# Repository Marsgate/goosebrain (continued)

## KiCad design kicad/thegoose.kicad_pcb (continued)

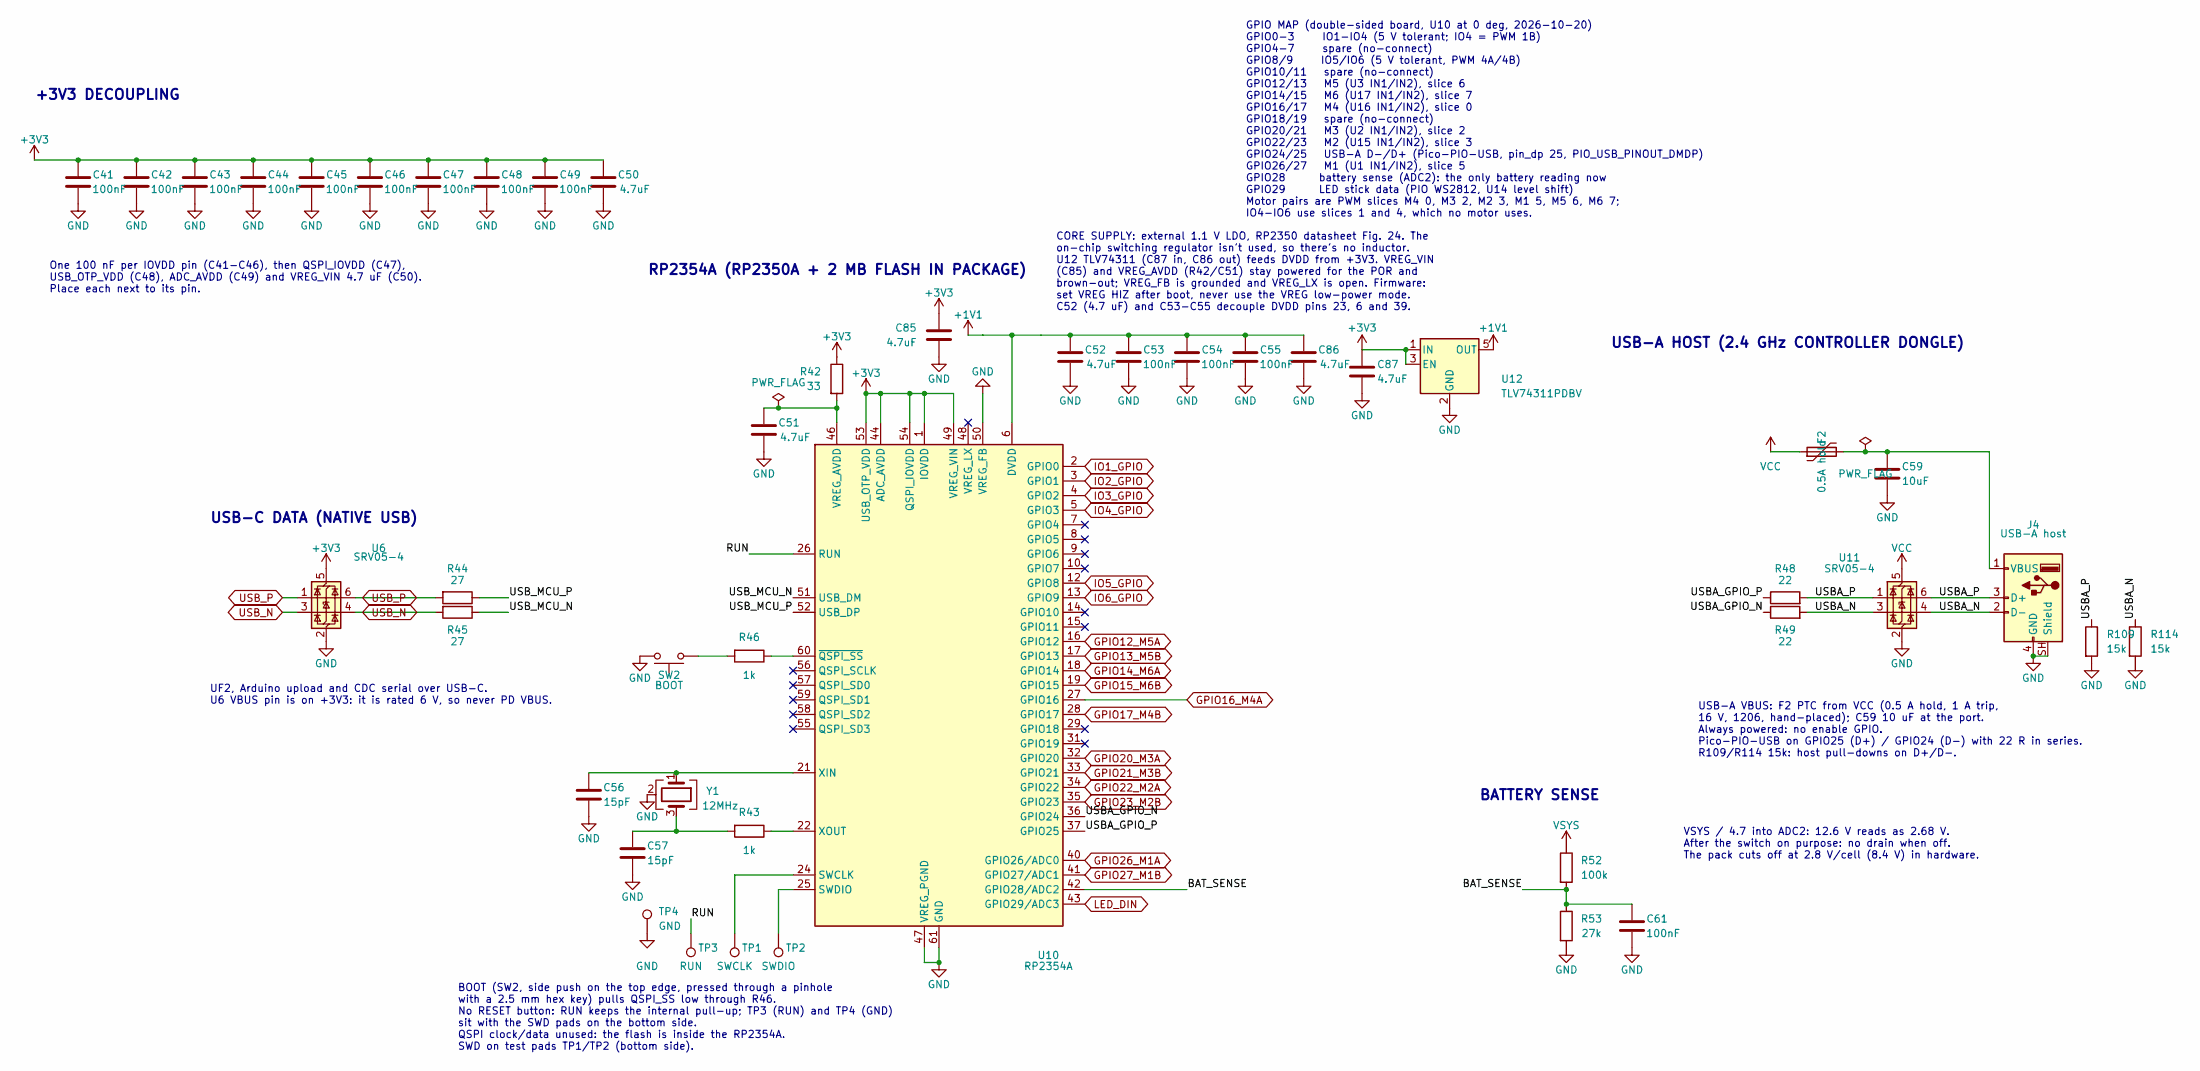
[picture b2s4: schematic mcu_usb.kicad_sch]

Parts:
C41, C42, C43, C44, C45, C46, C47, C48, C49, C53, C54, C55, C61: 100nF; C_0402_1005Metric; MPN CL05B104KO5NNNC; LCSC Part # C1525
C50, C51, C52, C85, C86, C87: 4.7uF; C_0402_1005Metric; MPN CL05A475MP5NRNC; LCSC Part # C23733
C56, C57: 15pF; C_0402_1005Metric; MPN 0402CG150J500NT; LCSC Part # C1548
C59: 10uF; C_0805_2012Metric; MPN CL21A106KAYNNNE; LCSC Part # C15850
F2: 0.5A hold; Fuse_1206_3216Metric; MPN JK-nSMD050-16; LCSC Part # C2680506
J4: USB-A host; USB_A_ShouHan_AF90_WJDG; MPN AF 90 WJDG; LCSC Part # C456018
R42: 33; R_0402_1005Metric; MPN 0402WGF330JTCE; LCSC Part # C25105
R43, R46: 1k; R_0402_1005Metric; MPN 0402WGF1001TCE; LCSC Part # C11702
R44, R45: 27; R_0603_1608Metric; MPN 0603WAF270JT5E; LCSC Part # C25190
R48, R49: 22; R_0402_1005Metric; MPN 0402WGF220JTCE; LCSC Part # C25092
R52: 100k; R_0402_1005Metric; MPN 0402WGF1003TCE; LCSC Part # C25741
R53: 27k; R_0402_1005Metric; MPN 0402WGF2702TCE; LCSC Part # C25771
R109, R114: 15k; R_0402_1005Metric; MPN 0402WGF1502TCE; LCSC Part # C25756
SW2: BOOT; SW_Push_1P1T-MP_NO_Horizontal_Alps_SKRTLAE010_JLC; MPN SKRTLAE010; LCSC Part # C110293
TP1: SWCLK; TestPoint_Pad_D1.0mm
TP2: SWDIO; TestPoint_Pad_D1.0mm
TP3: RUN; TestPoint_Pad_D1.0mm
TP4: GND; TestPoint_Pad_D1.0mm
U6, U11: SRV05-4; SOT-23-6; MPN SRV05-4; LCSC Part # C7420376
U10: RP2354A; QFN-60-1EP_7x7mm_P0.4mm_EP3.4x3.4mm; MPN RP2354A; LCSC Part # C41378174
U12: TLV74311PDBV; SOT-23-5; MPN TLV74311PDBVR; LCSC Part # C485147
Y1: 12MHz; Crystal_SMD_3225-4Pin_3.2x2.5mm; MPN ABM8-272-T3; LCSC Part # C20625731

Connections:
+1V1: C52.1, C53.1, C54.1, C55.1, C86.1, U10.6 (DVDD), U10.23 (DVDD), U10.39 (DVDD), U12.5 (OUT)
+3V3: C41.1, C42.1, C43.1, C44.1, C45.1, C46.1, C47.1, C48.1, C49.1, C50.1, C85.1, C87.1, R42.1, U6.5 (VP), U10.1 (IOVDD), U10.11 (IOVDD), U10.20 (IOVDD), U10.30 (IOVDD), U10.38 (IOVDD), U10.44 (ADC_AVDD), U10.45 (IOVDD), U10.49 (VREG_VIN), U10.53 (USB_OTP_VDD), U10.54 (QSPI_IOVDD), U12.1 (IN), U12.3 (EN); also elsewhere on the board
/MCU & USB/BAT_SENSE: C61.1, R52.2, R53.1, U10.42 (GPIO28/ADC2)
/MCU & USB/RUN: TP3.1 (1_1), U10.26 (RUN)
/MCU & USB/USBA_GPIO_N: R49.1, U10.36 (GPIO24)
/MCU & USB/USBA_GPIO_P: R48.1, U10.37 (GPIO25)
/MCU & USB/USBA_N: J4.2 (D-), R49.2, R114.1, U11.3 (IO2), U11.4 (IO3)
/MCU & USB/USBA_P: J4.3 (D+), R48.2, R109.1, U11.1 (IO1), U11.6 (IO4)
/MCU & USB/USB_MCU_N: R45.1, U10.51 (USB_DM)
/MCU & USB/USB_MCU_P: R44.1, U10.52 (USB_DP)
GND: C41.2, C42.2, C43.2, C44.2, C45.2, C46.2, C47.2, C48.2, C49.2, C50.2, C51.2, C52.2, C53.2, C54.2, C55.2, C56.2, C57.2, C59.2, C61.2, C85.2, C86.2, C87.2, J4.4 (GND), J4.SH (Shield), R53.2, R109.2, R114.2, SW2.2, TP4.1 (1_1), U6.2 (VN), U10.47 (VREG_PGND), U10.50 (VREG_FB), U10.61 (GND), U11.2 (VN), U12.2 (GND), Y1.2 (G), Y1.4 (G); also elsewhere on the board
GPIO12_M5A: U10.16 (GPIO12); also elsewhere on the board
GPIO13_M5B: U10.17 (GPIO13); also elsewhere on the board
GPIO14_M6A: U10.18 (GPIO14); also elsewhere on the board
GPIO15_M6B: U10.19 (GPIO15); also elsewhere on the board
GPIO16_M4A: U10.27 (GPIO16); also elsewhere on the board
GPIO17_M4B: U10.28 (GPIO17); also elsewhere on the board
GPIO20_M3A: U10.32 (GPIO20); also elsewhere on the board
GPIO21_M3B: U10.33 (GPIO21); also elsewhere on the board
GPIO22_M2A: U10.34 (GPIO22); also elsewhere on the board
GPIO23_M2B: U10.35 (GPIO23); also elsewhere on the board
GPIO26_M1A: U10.40 (GPIO26/ADC0); also elsewhere on the board
GPIO27_M1B: U10.41 (GPIO27/ADC1); also elsewhere on the board
IO1_GPIO: U10.2 (GPIO0); also elsewhere on the board
IO2_GPIO: U10.3 (GPIO1); also elsewhere on the board
IO3_GPIO: U10.4 (GPIO2); also elsewhere on the board
IO4_GPIO: U10.5 (GPIO3); also elsewhere on the board
IO5_GPIO: U10.12 (GPIO8); also elsewhere on the board
IO6_GPIO: U10.13 (GPIO9); also elsewhere on the board
LED_DIN: U10.43 (GPIO29/ADC3); also elsewhere on the board
unnamed: C57.1, R43.2, Y1.3
unnamed: C59.1, F2.2, J4.1 (VBUS)
unnamed: R46.2, SW2.1
unnamed: TP1.1 (1_1), U10.24 (SWCLK)
unnamed: TP2.1 (1_1), U10.25 (SWDIO)
unnamed: C51.1, R42.2, U10.46 (VREG_AVDD)
unnamed: C56.1, U10.21 (XIN), Y1.1
unnamed: R43.1, U10.22 (XOUT)
unnamed: R46.1, U10.60 (~QSPI_SS)
USB_N: R45.2, U6.3 (IO2), U6.4 (IO3); also elsewhere on the board
USB_P: R44.2, U6.1 (IO1), U6.6 (IO4); also elsewhere on the board
VCC: F2.1, U11.5 (VP); also elsewhere on the board
VSYS: R52.1; also elsewhere on the board

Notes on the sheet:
RP2354A (RP2350A + 2 MB FLASH IN PACKAGE)
UF2, Arduino upload and CDC serial over USB-C. U6 VBUS pin is on +3V3: it is rated 6 V, so never PD VBUS.
+3V3 DECOUPLING
CORE SUPPLY: external 1.1 V LDO, RP2350 datasheet Fig. 24. The on-chip switching regulator isn't used, so there's no inductor. U12 TLV74311 (C87 in, C86 out) feeds DVDD from +3V3. VREG_VIN (C85) and VREG_AVDD (R42/C51) stay powered for the POR and brown-out; VREG_FB is grounded and VREG_LX is open.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
BATTERY SENSE
VSYS / 4.7 into ADC2: 12.6 V reads as 2.68 V. After the switch on purpose: no drain when off. The pack cuts off at 2.8 V/cell (8.4 V) in hardware.
USB-C DATA (NATIVE USB)
One 100 nF per IOVDD pin (C41-C46), then QSPI_IOVDD (C47), USB_OTP_VDD (C48), ADC_AVDD (C49) and VREG_VIN 4.7 uF (C50). Place each next to its pin.
USB-A VBUS: F2 PTC from VCC (0.5 A hold, 1 A trip, 16 V, 1206, hand-placed); C59 10 uF at the port. Always powered: no enable GPIO. Pico-PIO-USB on GPIO25 (D+) / GPIO24 (D-) with 22 R in series. R109/R114 15k: host pull-downs on D+/D-.
USB-A HOST (2.4 GHz CONTROLLER DONGLE)
BOOT (SW2, side push on the top edge, pressed through a pinhole with a 2.5 mm hex key) pulls QSPI_SS low through R46. No RESET button: RUN keeps the internal pull-up; TP3 (RUN) and TP4 (GND) sit with the SWD pads on the bottom side. QSPI clock/data unused: the flash is inside the RP2354A. SWD on te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
GPIO MAP (double-sided board, U10 at 0 deg, 2026-10-20) GPIO0-3 IO1-IO4 (5 V tolerant; IO4 = PWM 1B) GPIO4-7 spare (no-connect) GPIO8/9 IO5/IO6 (5 V tolerant, PWM 4A/4B) GPIO10/11 spare (no-connect) GPIO12/13 M5 (U3 IN1/IN2), slice 6 GPIO14/15 M6 (U17 IN1/IN2), slice 7 GPIO16/17 M4 (U16 IN1/IN2), s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

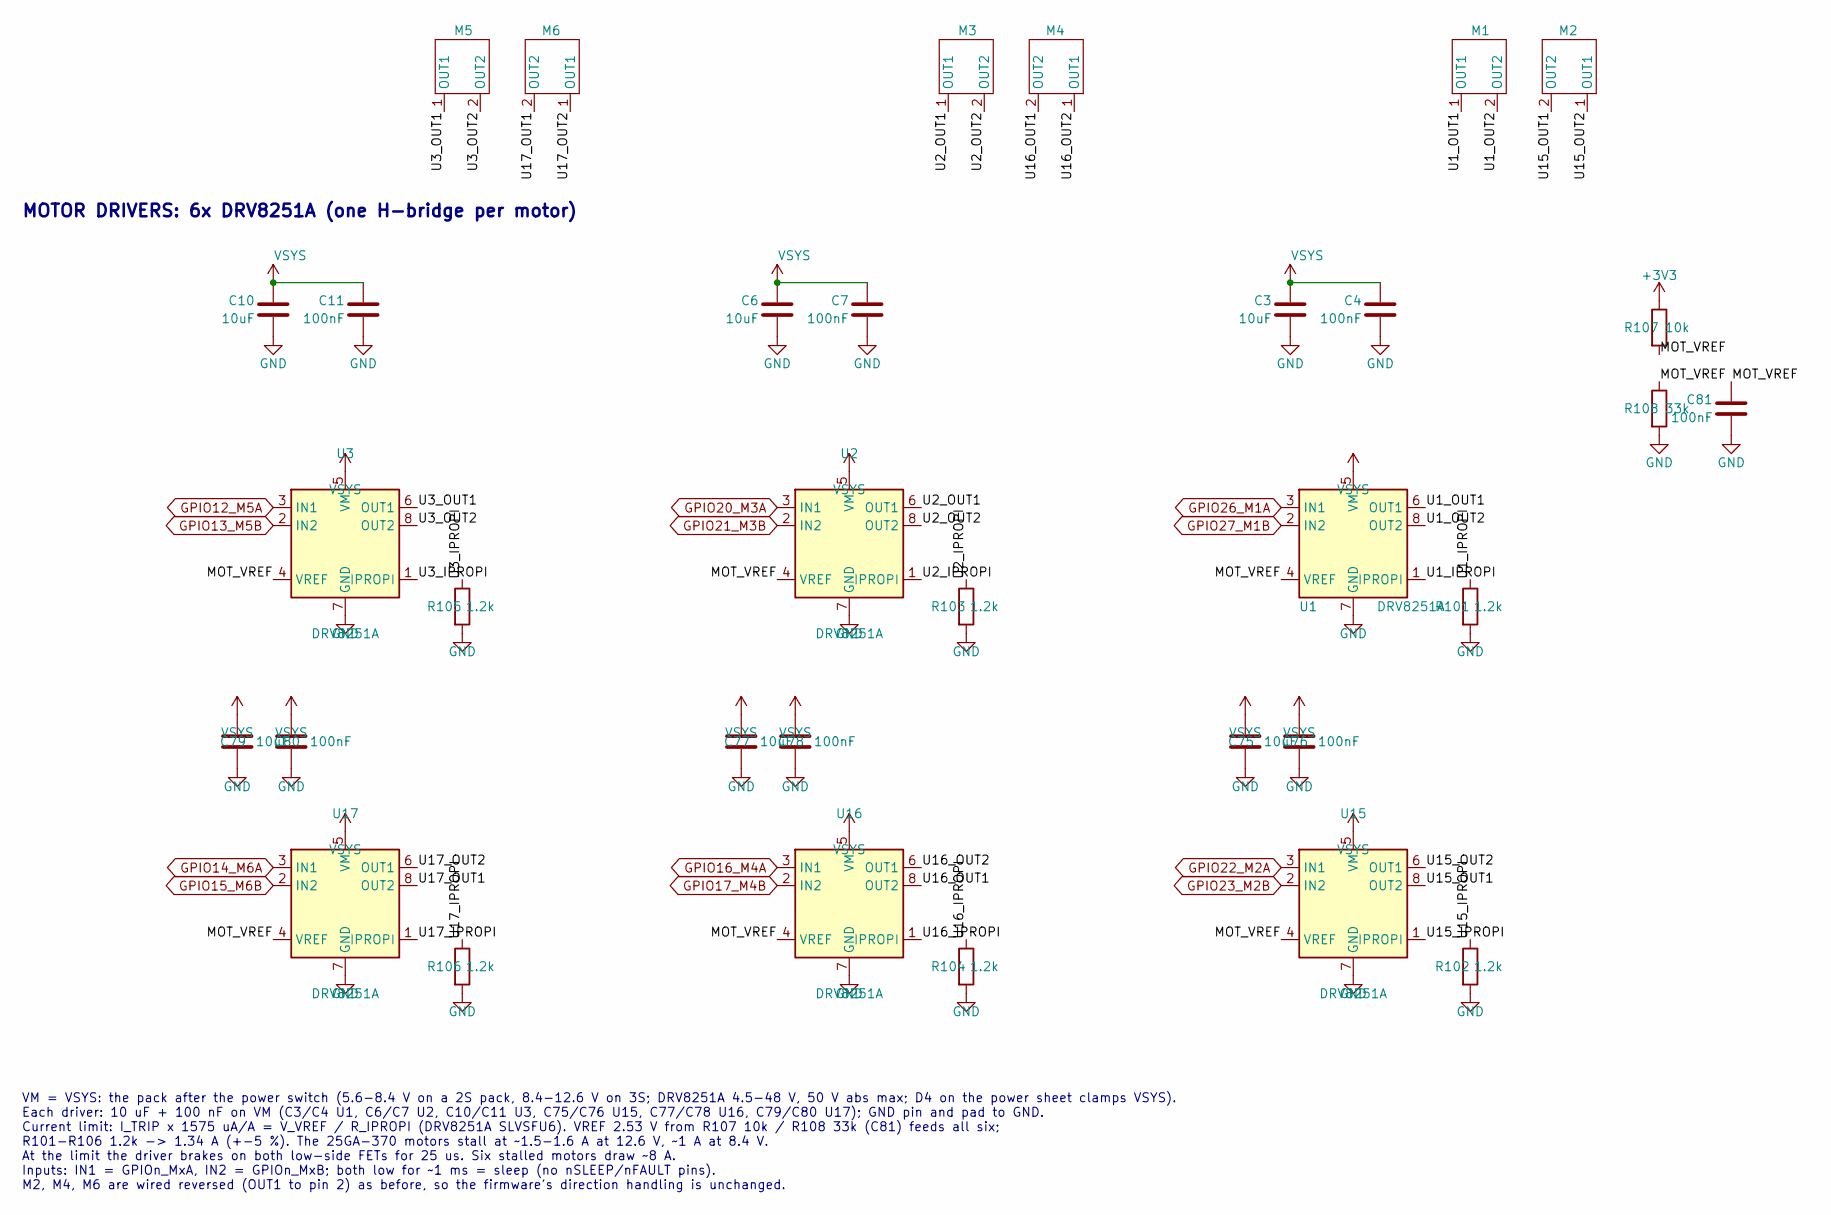
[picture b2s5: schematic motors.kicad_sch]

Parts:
C3, C6, C10, C75, C77, C79: 10uF; C_0805_2012Metric; MPN CL21A106KAYNNNE; LCSC Part # C15850
C4, C7, C11, C76, C78, C80: 100nF; C_0805_2012Metric; MPN CC0805KRX7R9BB104; LCSC Part # C49678
C81: 100nF; C_0402_1005Metric; MPN CL05B104KO5NNNC; LCSC Part # C1525
M1, M2, M3, M4, M5, M6: JST_PH_S2B-PH-K_1x02_P2.00mm_Horizontal; MPN S2B-PH-K-S(LF)(SN); LCSC Part # C173752
R101, R102, R103, R104, R105, R106: 1.2k; R_0402_1005Metric; MPN 0402WGF1201TCE; LCSC Part # C25862
R107: 10k; R_0402_1005Metric; MPN 0402WGF1002TCE; LCSC Part # C25744
R108: 33k; R_0402_1005Metric; MPN 0402WGF3302TCE; LCSC Part # C25779
U1, U2, U3, U15, U16, U17: DRV8251A; Texas_HTSOP-8-1EP_3.9x4.9mm_P1.27mm_EP2.95x4.9mm_Mask2.4x3.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; MPN DRV8251ADDAR; LCSC Part # C5218844

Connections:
+3V3: R107.1; also elsewhere on the board
/Motor drivers/MOT_VREF: C81.1, R107.2, R108.1, U1.4 (VREF), U2.4 (VREF), U3.4 (VREF), U15.4 (VREF), U16.4 (VREF), U17.4 (VREF)
/Motor drivers/U1_IPROPI: R101.1, U1.1 (IPROPI)
/Motor drivers/U1_OUT1: M1.1 (OUT1), U1.6 (OUT1)
/Motor drivers/U1_OUT2: M1.2 (OUT2), U1.8 (OUT2)
/Motor drivers/U2_IPROPI: R103.1, U2.1 (IPROPI)
/Motor drivers/U2_OUT1: M3.1 (OUT1), U2.6 (OUT1)
/Motor drivers/U2_OUT2: M3.2 (OUT2), U2.8 (OUT2)
/Motor drivers/U3_IPROPI: R105.1, U3.1 (IPROPI)
/Motor drivers/U3_OUT1: M5.1 (OUT1), U3.6 (OUT1)
/Motor drivers/U3_OUT2: M5.2 (OUT2), U3.8 (OUT2)
/Motor drivers/U15_IPROPI: R102.1, U15.1 (IPROPI)
/Motor drivers/U15_OUT1: M2.2 (OUT2), U15.8 (OUT2)
/Motor drivers/U15_OUT2: M2.1 (OUT1), U15.6 (OUT1)
/Motor drivers/U16_IPROPI: R104.1, U16.1 (IPROPI)
/Motor drivers/U16_OUT1: M4.2 (OUT2), U16.8 (OUT2)
/Motor drivers/U16_OUT2: M4.1 (OUT1), U16.6 (OUT1)
/Motor drivers/U17_IPROPI: R106.1, U17.1 (IPROPI)
/Motor drivers/U17_OUT1: M6.2 (OUT2), U17.8 (OUT2)
/Motor drivers/U17_OUT2: M6.1 (OUT1), U17.6 (OUT1)
GND: C3.1, C4.2, C6.1, C7.2, C10.1, C11.2, C75.2, C76.2, C77.2, C78.2, C79.2, C80.2, C81.2, R101.2, R102.2, R103.2, R104.2, R105.2, R106.2, R108.2, U1.7 (GND), U1.9 (GND), U2.7 (GND), U2.9 (GND), U3.7 (GND), U3.9 (GND), U15.7 (GND), U15.9 (GND), U16.7 (GND), U16.9 (GND), U17.7 (GND), U17.9 (GND); also elsewhere on the board
GPIO12_M5A: U3.3 (IN1); also elsewhere on the board
GPIO13_M5B: U3.2 (IN2); also elsewhere on the board
GPIO14_M6A: U17.3 (IN1); also elsewhere on the board
GPIO15_M6B: U17.2 (IN2); also elsewhere on the board
GPIO16_M4A: U16.3 (IN1); also elsewhere on the board
GPIO17_M4B: U16.2 (IN2); also elsewhere on the board
GPIO20_M3A: U2.3 (IN1); also elsewhere on the board
GPIO21_M3B: U2.2 (IN2); also elsewhere on the board
GPIO22_M2A: U15.3 (IN1); also elsewhere on the board
GPIO23_M2B: U15.2 (IN2); also elsewhere on the board
GPIO26_M1A: U1.3 (IN1); also elsewhere on the board
GPIO27_M1B: U1.2 (IN2); also elsewhere on the board
VSYS: C3.2, C4.1, C6.2, C7.1, C10.2, C11.1, C75.1, C76.1, C77.1, C78.1, C79.1, C80.1, U1.5 (VM), U2.5 (VM), U3.5 (VM), U15.5 (VM), U16.5 (VM), U17.5 (VM); also elsewhere on the board

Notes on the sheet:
MOTOR DRIVERS: 6x DRV8251A (one H-bridge per motor)
VM = VSYS: the pack after the power switch (5.6-8.4 V on a 2S pack, 8.4-12.6 V on 3S; DRV8251A 4.5-48 V, 50 V abs max; D4 on the power sheet clamps VSYS). Each driver: 10 uF + 100 nF on VM (C3/C4 U1, C6/C7 U2, C10/C11 U3, C75/C76 U15, C77/C78 U16, C79/C80 U17); GND pin and pad to GND. Current limit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

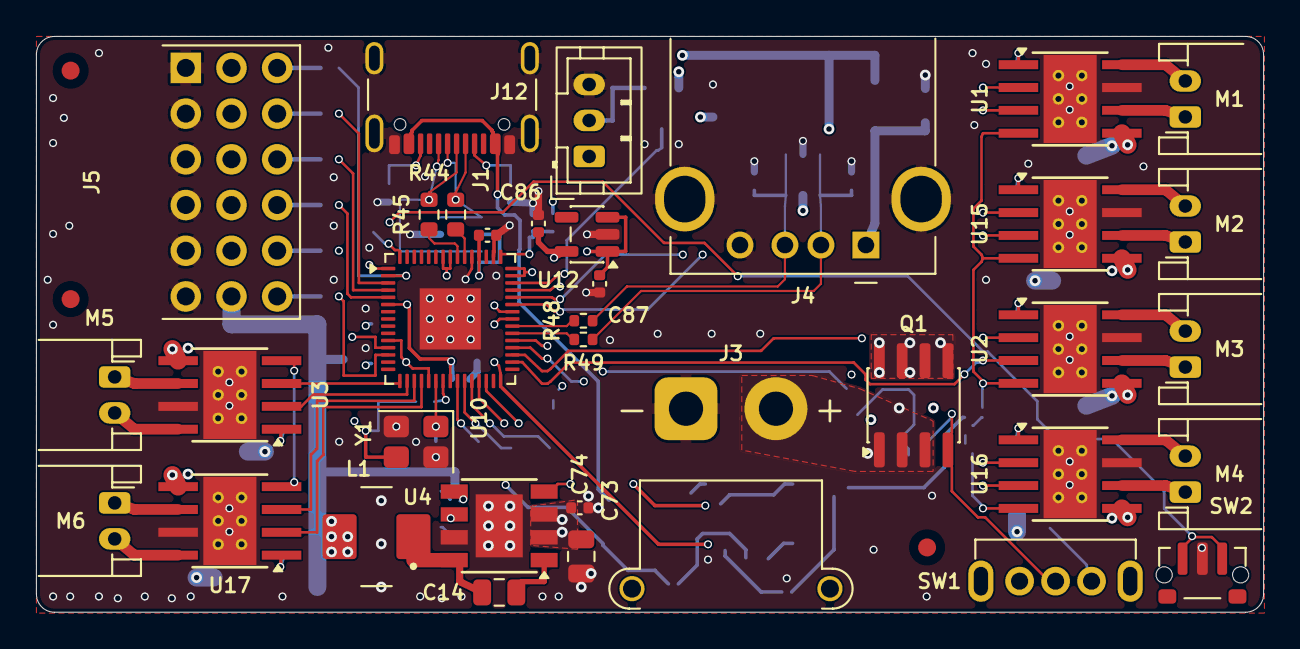
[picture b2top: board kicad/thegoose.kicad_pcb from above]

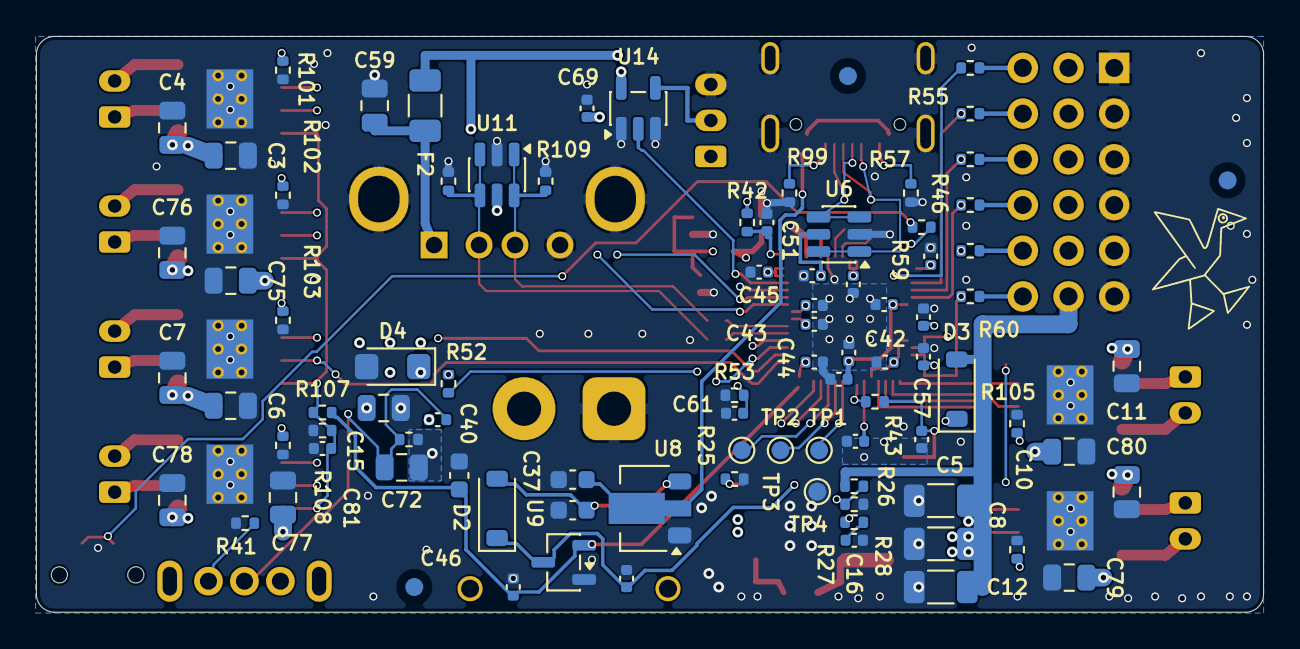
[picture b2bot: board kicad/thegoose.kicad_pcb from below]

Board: 6 copper layers, 68.2 x 32.0 mm, 127 parts (89 on the bottom side), 83 nets.

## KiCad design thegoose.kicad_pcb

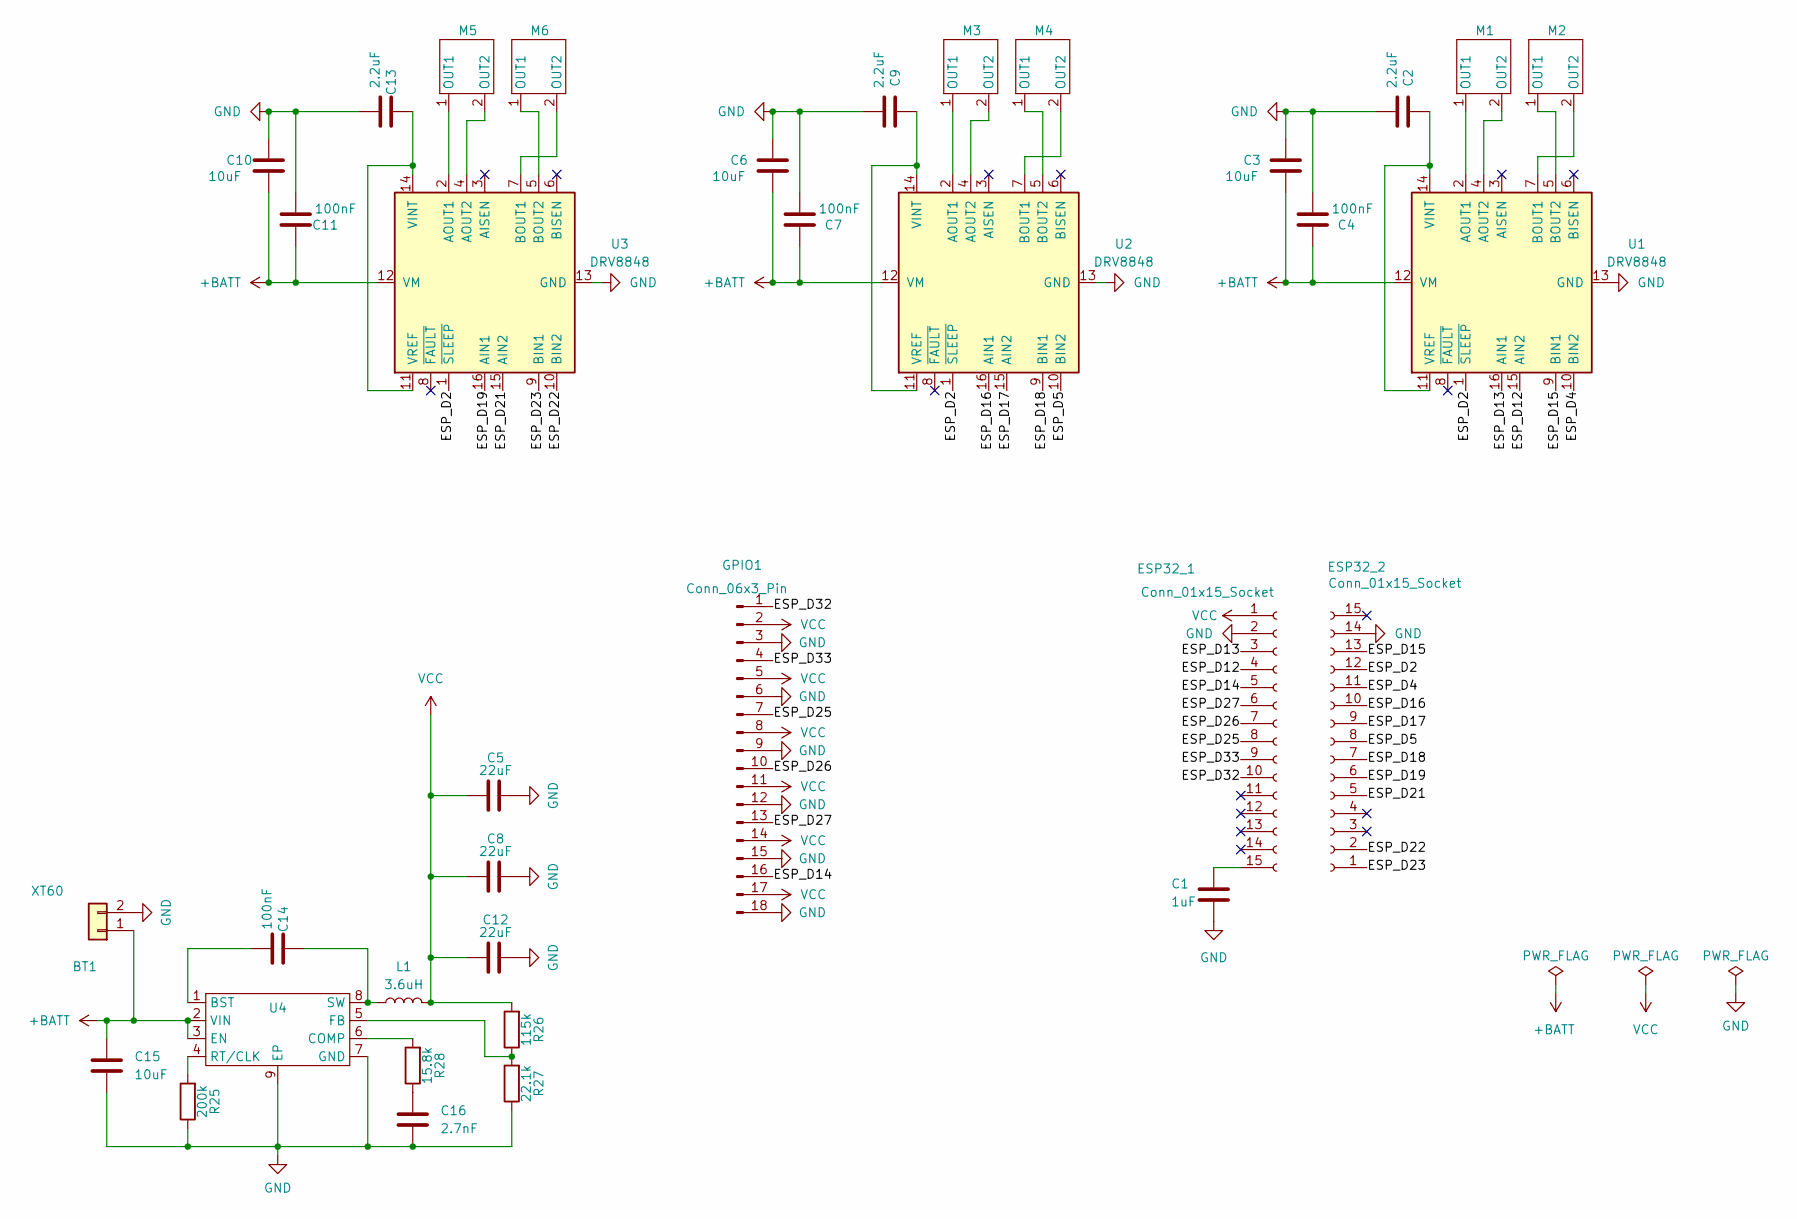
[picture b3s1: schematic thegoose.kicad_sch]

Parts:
BT1: XT60; AMASS_XT60PW-M_1x02_P7.20mm_Horizontal; LCSC Part # C98732
C1: 1uF; C_0805_2012Metric; LCSC Part # C28323
C2, C9, C13: 2.2uF; C_0805_2012Metric; LCSC Part # C377773
C3, C6, C10, C15: 10uF; C_0805_2012Metric; LCSC Part # C15850
C4, C7, C11, C14: 100nF; C_0805_2012Metric; LCSC Part # C49678
C5, C8, C12: 22uF; C_0603_1608Metric; LCSC Part # C59461
C16: 2.7nF; C_0603_1608Metric; LCSC Part # C302024
ESP32_1, ESP32_2: Conn_01x15_Socket; PinSocket_1x15_P2.54mm_Vertical; LCSC Part # C2932676
GPIO1: Conn_06x3_Pin; PinHeader_3x06_P2.54mm_Horizontal; LCSC Part # C42431837
L1: 3.6uH; L_Wurth_WE-LQSH-4020; LCSC Part # C7588667
M1, M2, M3, M4, M5, M6: JST_XH_S2B-XH-A_1x02_P2.50mm_Horizontal; LCSC Part # C157931
R25: 200k; R_0805_2012Metric_Pad1.20x1.40mm_HandSolder; LCSC Part # C844827
R26: 115k; R_0805_2012Metric_Pad1.20x1.40mm_HandSolder; LCSC Part # C5200544
R27: 22.1k; R_0805_2012Metric_Pad1.20x1.40mm_HandSolder; LCSC Part # C228640
R28: 15.8k; R_0805_2012Metric_Pad1.20x1.40mm_HandSolder; LCSC Part # C47115540
U1, U2, U3: DRV8848; TSSOP-16-1EP_4.4x5mm_P0.65mm; LCSC Part # C131079
U4: AP64500SP-13; Diodes_SO-8EP; LCSC Part # C2070920

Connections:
+BATT: BT1.1, C3.2, C4.1, C6.2, C7.1, C10.2, C11.1, C15.2, U1.12 (VM), U2.12 (VM), U3.12 (VM), U4.2 (VIN), U4.3 (EN)
/ESP_D2: ESP32_2.12, U1.1 (~SLEEP), U2.1 (~SLEEP), U3.1 (~SLEEP)
/ESP_D4: ESP32_2.11, U1.10 (BIN2)
/ESP_D5: ESP32_2.8, U2.10 (BIN2)
/ESP_D12: ESP32_1.4, U1.15 (AIN2)
/ESP_D13: ESP32_1.3, U1.16 (AIN1)
/ESP_D14: ESP32_1.5, GPIO1.16
/ESP_D15: ESP32_2.13, U1.9 (BIN1)
/ESP_D16: ESP32_2.10, U2.16 (AIN1)
/ESP_D17: ESP32_2.9, U2.15 (AIN2)
/ESP_D18: ESP32_2.7, U2.9 (BIN1)
/ESP_D19: ESP32_2.6, U3.16 (AIN1)
/ESP_D21: ESP32_2.5, U3.15 (AIN2)
/ESP_D22: ESP32_2.2, U3.10 (BIN2)
/ESP_D23: ESP32_2.1, U3.9 (BIN1)
/ESP_D25: ESP32_1.8, GPIO1.7
/ESP_D26: ESP32_1.7, GPIO1.10
/ESP_D27: ESP32_1.6, GPIO1.13
/ESP_D32: ESP32_1.10, GPIO1.1
/ESP_D33: ESP32_1.9, GPIO1.4
GND: BT1.2, C1.2, C2.2, C3.1, C4.2, C5.2, C6.1, C7.2, C8.2, C9.2, C10.1, C11.2, C12.2, C13.2, C15.1, C16.1, ESP32_1.2, ESP32_2.14, GPIO1.3, GPIO1.6, GPIO1.9, GPIO1.12, GPIO1.15, GPIO1.18, R25.1, R27.1, U1.13 (GND), U1.17 (GND), U2.13 (GND), U2.17 (GND), U3.13 (GND), U3.17 (GND), U4.7 (GND), U4.9 (EP)
unnamed: C16.2, R28.1
unnamed: C1.1, ESP32_1.15
unnamed: M1.1 (OUT1), U1.2 (AOUT1)
unnamed: M1.2 (OUT2), U1.4 (AOUT2)
unnamed: M2.1 (OUT1), U1.5 (BOUT2)
unnamed: M2.2 (OUT2), U1.7 (BOUT1)
unnamed: M3.1 (OUT1), U2.2 (AOUT1)
unnamed: M3.2 (OUT2), U2.4 (AOUT2)
unnamed: M4.1 (OUT1), U2.5 (BOUT2)
unnamed: M4.2 (OUT2), U2.7 (BOUT1)
unnamed: M5.1 (OUT1), U3.2 (AOUT1)
unnamed: M5.2 (OUT2), U3.4 (AOUT2)
unnamed: M6.1 (OUT1), U3.5 (BOUT2)
unnamed: M6.2 (OUT2), U3.7 (BOUT1)
unnamed: C2.1, U1.11 (VREF), U1.14 (VINT)
unnamed: C9.1, U2.11 (VREF), U2.14 (VINT)
unnamed: C13.1, U3.11 (VREF), U3.14 (VINT)
unnamed: C14.2, U4.1 (BST)
unnamed: R28.2, U4.6 (COMP)
unnamed: R26.1, R27.2, U4.5 (FB)
unnamed: R25.2, U4.4 (RT/CLK)
unnamed: C14.1, L1.1, U4.8 (SW)
VCC: C5.1, C8.1, C12.1, ESP32_1.1, GPIO1.2, GPIO1.5, GPIO1.8, GPIO1.11, GPIO1.14, GPIO1.17, L1.2, R26.2

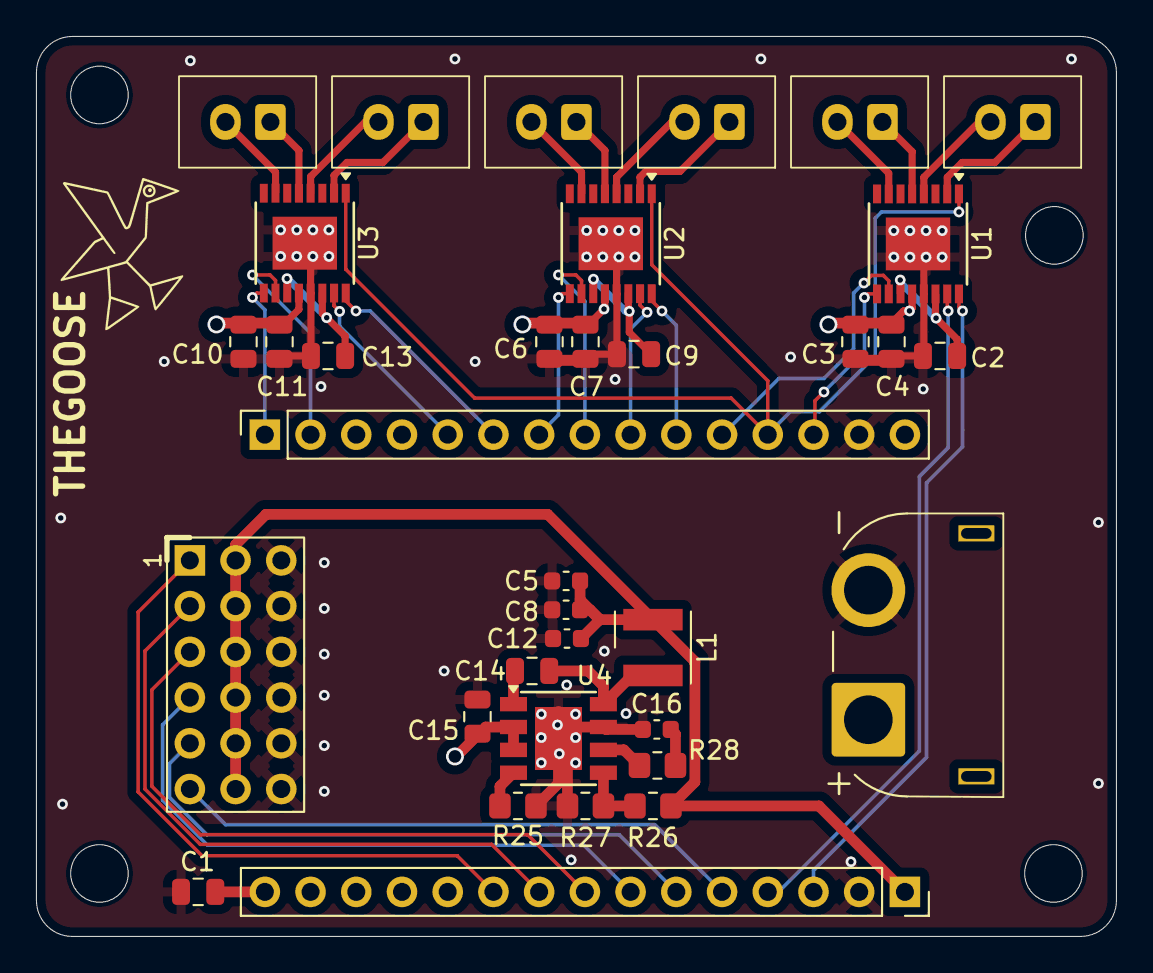
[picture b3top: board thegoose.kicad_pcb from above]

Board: 4 copper layers, 60.0 x 50.0 mm, 35 parts (0 on the bottom side), 44 nets.

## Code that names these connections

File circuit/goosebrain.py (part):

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    # Pack connector: a vertical male XT30 (Amass XT30UPB-M) on top beside the
    # pack's lead end; the pack's female XT30U-F plugs straight in. Pin 1 is
    # "-" at the keyed (chamfered) end: the pack's negative, which goes to the
    # protector's low side (BAT_N), not board GND. Pin 2 is "+" (PACK+).
    # Mated with the lead bent toward the pack it stands about 22-24 mm, close
    # to the face (23.4 mm): see PARTS.md.
    j = part(
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

@subcircuit
def mcu(v3v3, gnd, usb_dp, usb_dm, gpio):
    """RP2354A with the Raspberry Pi minimal-design support parts.

    gpio maps GPIO number -> net for every GPIO this board uses. The RP2354A
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    GND 3k-2. Refs stay stable: J6-J10 are burned.

    330 Ohm series resistors protect the GPIOs from shorts and hot-plugging.
    IO1-IO4 are on 5 V tolerant GPIOs; IO5/IO6 are on GPIO26/27 (ADC), which
    are not, so IO5/IO6 must stay at 3.3 V logic.
    """
    j = None
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
@subcircuit
def battery_sense(vsys, sense, gnd):
    """VSYS / 4.7 into an ADC pin: 12.6 V reads as about 2.68 V."""
    # On VSYS, after the power switch, so the divider drains nothing when the
    # switch is off. With the switch off, read the pack from the BQ25798 ADC.
    res(ref("R"), "100k", "0402", vsys, sense)
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for rail in (vbus, vbat, vsys, vcc, v3v3, regn, gnd, bat_n):
    rail.drive = POWER

# GPIO map (RP2354A, GPIO0-29), chosen in the PCB layout so each signal leaves
# U10 on the side facing its destination (pin-swap pass redone again on
# 2026-10-17, after the IO ports moved to the left end; IO1-IO4 reordered for the
# recessed header so U10's pin order matches S1-S6). Each motor's two inputs are one PWM slice's
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# swapped" means the motor's IN1 is on the odd GPIO (PWM channel B); the
# firmware maps direction per motor.
#
#   GPIO0-1   M3 (U2 AIN1/AIN2)                GPIO14-15 M4 (U2 BIN1/BIN2)
#   GPIO2     USB-A D+ (PIO-USB)               GPIO16  IO1
#   GPIO3     USB-A D- (PIO-USB, D+ + 1)       GPIO17  I2C0 SCL (charger)
#   GPIO4-5   M1 (U1 AIN1/AIN2)                GPIO18  LED stick data (PIO WS2812)
#   GPIO6-7   M2 (U1 BIN2/BIN1, A/B swapped)   GPIO19  driver nFAULT (wired-OR)
#   GPIO8     I2C0 SDA (charger)               GPIO20  spare
#   GPIO9     charger /INT                     GPIO21  IO2
#   GPIO10-11 M5 (U3 AIN1/AIN2)                GPIO22  IO3
#   GPIO12-13 M6 (U3 BIN2/BIN1, A/B swapped)   GPIO23  driver nSLEEP (all three)
#   GPIO24    IO4                              GPIO25  USB-A VBUS enable
#   GPIO26-27 IO5, IO6 (ADC0-1, 3.3 V only)    GPIO28  battery sense (ADC2)
#   GPIO29    spare (ADC3)
#
# PWM slices: M3 0, M1 2, M2 3, M5 5, M6 6, M4 7. IO1-IO4 are 5 V tolerant
# (GPIO0-25); servos on the IO ports run from PIO.
MOTOR_GPIO = {  # motor -> (IN1 GPIO, IN2 GPIO); the net is GPIO<n>_<motor><A|B>
    "M1": (4, 5), "M2": (7, 6), "M3": (0, 1),
    "M4": (14, 15), "M5": (10, 11), "M6": (13, 12),
}
GPIO_NETS = {
    2: "USBA_GPIO_P", 3: "USBA_GPIO_N", 8: "I2C_SDA", 9: "CHG_INT", 16: "IO1_GPIO",
    17: "I2C_SCL", 18: "LED_DIN", 19: "DRV_FAULT", 21: "IO2_GPIO",
    22: "IO3_GPIO", 23: "DRV_SLEEP", 24: "IO4_GPIO", 25: "USBA_VBUS_EN",
    26: "IO5_GPIO", 27: "IO6_GPIO", 28: "BAT_SENSE",
}
GP = {name: n for n, name in GPIO_NETS.items()}  # signal name -> GPIO number
gpio = {n: Net(f"GPIO{n}_{m}{ab}") for m, pins in MOTOR_GPIO.items() for n, ab in zip(pins, "AB")}
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battery_and_switch(vbat, vsys, bat_n, gnd)
buck_5v(vsys, vcc, gnd)
rail_3v3(vbus, vcc, v3v3, gnd)
mcu(v3v3, gnd, usb_dp, usb_dm, gpio)
usb_a_host(sig("USBA_GPIO_P"), sig("USBA_GPIO_N"), sig("USBA_VBUS_EN"), vcc, gnd)
ref("R"); ref("LED")  # R51 and LED2 burned: the GPIO status LED was removed (the LED stick shows status)
battery_sense(vsys, sig("BAT_SENSE"), gnd)
res(ref("R"), "10k", "0402", v3v3, sig("DRV_FAULT"))  # nFAULT pull-up
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
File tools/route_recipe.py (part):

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rest afterwards and treats the locked copper as fixed. Coordinates come from pad positions, so they follow the parts.

U10 (RP2354A) sits at 0 deg: W column = pins 1-15 (pin 1 at the top), S row = pins 16-30 (16 at the west end),
E column = pins 31-45 (31 at the bottom), N row = pins 46-60 (46 at the east end). Pad pitch 0.4 mm; the pads run
from 3.05 to 3.85 mm off the centre and the exposed pad is 3.4 mm square.
"""
import sys
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AVDD = "Net-(U10-VREG_AVDD)"
SW, BST = "Net-(U4-SW)", "Net-(U4-BST)"
USB = {"P": "USB_P", "N": "USB_N", "MP": "/MCU & USB/USB_MCU_P", "MN": "/MCU & USB/USB_MCU_N",
       "AP": "/MCU & USB/USBA_P", "AN": "/MCU & USB/USBA_N", "GP": "/MCU & USB/USBA_GPIO_P",
       "GN": "/MCU & USB/USBA_GPIO_N"}
WU = 0.124                  # USB pair track width (90 ohm at a 0.127 mm gap on JLC06161H-3313, see thegoose.kicad_dru)
GU = 0.127                  # USB pair gap

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# ---------------------------------------------------------------------------------------------------------------------
# U10 west side: IO1-IO6 to the vias in R55-R60's U10-side pads (a column at x 16.81, one per J5 row). Between that
# column and the pins there is room for three F.Cu lanes west of C41's vias and J1's shell peg, so:
# - IO2-IO4 (pins 3-5) run straight west and turn north on lanes 0.32 mm apart, the higher pin on the eastern lane.
# - IO1 (pin 2) drops through a via just inside the pin ring and runs north on B.Cu, between C41 and the R column and
#   west of J1's shell pegs. (On In2, its GND channel in In3 would cut the VCC band off from the VCC block.)
# - IO5 (pin 12) runs up the strip between the pin toes and C47/C50's vias, west between C47's two vias, and drops to
#   In2 for the run north (it would cross IO1-IO4 on F.Cu).
# - IO6 (pin 13) runs down the same strip, under C50, and north on F.Cu to its via.
# ---------------------------------------------------------------------------------------------------------------------
W_LANES = {"IO2_GPIO": 17.92, "IO3_GPIO": 17.60, "IO4_GPIO": 17.285}   # IO4 0.25 mm from IO5's 0.3 mm via hole


def u10_west(r):
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    for sig, x in W_LANES.items():
        q, v = ends(sig)
        top = v[1] + (x - v[0])                       # 45-degree run into the via from the south-east
        if sig == "IO4_GPIO":                         # bottom pin: step onto its lane with a 45-degree jog
            r.track(sig, "F", [q, (x + 0.2, q[1]), (x, q[1] - 0.2), (x, top), v], w)
        else:
            r.track(sig, "F", [q, (x, q[1]), (x, top), v], w)
    q, v = ends("IO1_GPIO")
    vi = (q[0] + 1.0, q[1])
    r.track("IO1_GPIO", "F", [q, vi], w)
    r.via("IO1_GPIO", *vi)
    x = 17.9
    r.track("IO1_GPIO", "B", [vi, (x, vi[1]), (x, v[1] + (x - v[0])), v], w)
    q, v = ends("IO5_GPIO")
    xs = q[0] - 0.71                                  # the strip between the pin toes and the 18.3 via column
    vi = (17.55, 16.7)
    r.track("IO5_GPIO", "F", [q, (xs, q[1]), (xs, vi[1]), vi], w)
    r.via("IO5_GPIO", *vi)
    r.track("IO5_GPIO", "2", [vi, (vi[0], v[1] + (vi[0] - v[0])), v], w)
    q, v = ends("IO6_GPIO")
    x = 17.075                                       # 0.25 mm from IO5's via hole
    r.track("IO6_GPIO", "F", [q, (xs, q[1]), (xs, 18.85), (x, 18.85), (x, v[1] + (x - v[0])), v], w)


# ---------------------------------------------------------------------------------------------------------------------
# U10 south-west: M5 and M6 (pins 16-19) to the IN pins of U3 and U17. The four lines run west in the strip between
# the pin toes and Y1's top pads, each pin one lane lower than the pin west of it, so nothing crosses: M5A straight
# across to U3, M5B down to U3's IN2, M6A and M6B down two lanes east of U3 to U17. No signal runs over the crystal.
# ---------------------------------------------------------------------------------------------------------------------
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    p = {n: r.pad("U10", n) for n in (16, 17, 18, 19)}
    u3 = {n: r.pad("U3", n) for n in (2, 3)}
    u17 = {n: r.pad("U17", n) for n in (2, 3)}
    r.track("GPIO12_M5A", "F", [p[16], (p[16][0], u3[3][1]), u3[3]], w)
    y = 19.9
    xd = u3[2][0] + 1.1 + (u3[2][1] - y)              # 45 degrees down into U3 pin 2, ending at its toe
    r.track("GPIO13_M5B", "F", [p[17], (p[17][0], y), (xd, y), (u3[2][0] + 1.1, u3[2][1]), u3[2]], w)
    # M6A/M6B: south at x 15.6/15.95 past M5B's diagonal, then 0.35 mm west, clear of L1's VCC pad
    for pin, net, y, x, yj, dst in ((18, "GPIO14_M6A", 20.25, 15.6, 22.9, u17[3]),
                                    (19, "GPIO15_M6B", 20.6, 15.95, 23.25, u17[2])):
        r.track(net, "F", [p[pin], (p[pin][0], y), (x, y), (x, yj), (x - 0.35, yj + 0.35), (x - 0.35, dst[1]), dst], w)


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

# ---------------------------------------------------------------------------------------------------------------------
# USB-A. U10 pins 37 (D+) / 36 (D-) east through R48/R49 (22 R at the source), then a coupled run along the gap between
# J4's pins and J3's body, up into J4 pins 3 (D+) and 2 (D-). U11 (ESD) and the 15k host pull-downs R109/R114 sit on
# the back on J4's own pins, so the pair needs no vias.
# ---------------------------------------------------------------------------------------------------------------------
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    xs = r48g[0] - 0.42                              # straight east between the escape groups, then fan to R48/R49
    r.track(USB["GP"], "F", [u37, (xs, u37[1]), (xs + abs(u37[1] - r48g[1]), r48g[1]), r48g], WU)
    r.track(USB["GN"], "F", [u36, (xs, u36[1]), (xs + abs(u36[1] - r49g[1]), r49g[1]), r49g], WU)
    yp = jp[1] + 2.3                                 # coupled run between J4's pins and J3's pads: D+ on top
    yn = yp + WU + GU
    r.track(USB["AP"], "F", [r48a, (r48a[0] + abs(r48a[1] - yp), yp), (jp[0] - 0.4, yp), (jp[0], yp - 0.4), jp], WU)
    r.track(USB["AN"], "F", [r49a, (r49a[0] + abs(r49a[1] - yn), yn), (jn[0] - 0.4, yn), (jn[0], yn - 0.4), jn], WU)
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

# ---------------------------------------------------------------------------------------------------------------------
# Motor drivers. OUT1/OUT2 run straight to their PH connector at 0.6 mm. VM (pin 5) drops through two vias in the
# 100 nF cap's VSYS pad on the back into the In3 VSYS area; the 10 uF joins on the back. IPROPI leaves pin 1 through a via
# beside the pin to its 1.2k on the back. GND (pin 7, exposed pad) is the F.Cu pour plus the footprint's thermal vias.
# ---------------------------------------------------------------------------------------------------------------------
DRIVERS = [("U1", "M1", "C4", "C3", "R101"), ("U15", "M2", "C76", "C75", "R102"), ("U2", "M3", "C7", "C6", "R103"),
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

# ---------------------------------------------------------------------------------------------------------------------
# Battery entry: PACK+ from J3 pad 2 to Q1's source pins as an F.Cu pour; Q1's drain pins in a VSYS pour with vias into
# the In3 VSYS area; the gate network (R40, C72 from PACK+, C71 to VSYS) on the back under Q1.
# ---------------------------------------------------------------------------------------------------------------------
def battery(r):
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           priority=20, clearance=0.2, min_w=0.25, solid=True, name="PACK+ J3-Q1")
    yd = drn[0][1]
    xa, xb = min(q[0] for q in drn) - 0.45, max(q[0] for q in drn) + 0.28
    r.zone("VSYS", "F", [(xa, yd - 1.45), (xb, yd - 1.45), (xb, yd + 0.98), (xa, yd + 0.98)], priority=20,
           clearance=0.2, min_w=0.25, solid=True, name="VSYS Q1 drain")
    r.vias_where_free("VSYS", [(x, yd - 1.0) for x in (xa + 0.45, xa + 1.3, xa + 2.15, xa + 3.0, xa + 3.85)] +
                      [(x, yd + 0.65) for x in (xa + 0.45, xa + 1.3, xa + 2.15, xa + 3.0, xa + 3.85)], d=0.6, drill=0.3)
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    # J12 data out of U14 to J12 pin 2, inside the band
    j2, u4 = r.pad("J12", "2"), r.padof("U14", "Net-(J12-Pin_2)")
    r.track("Net-(J12-Pin_2)", "B", [u4, (j2[0] + 1.3, u4[1]), (j2[0] + 1.3, j2[1]), j2], 0.25)
    # LED_DIN arrives on F.Cu; a via by U14 pin 2 drops it inside the band
    ld = r.padof("U14", "LED_DIN")
    vl = r.via("LED_DIN", ld[0], ld[1] + 1.05)
    r.track("LED_DIN", "B", [ld, vl], 0.2)
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
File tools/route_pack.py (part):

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  under the fuse. J2's and J3's barrels reach every layer.
- the charger's power stage on F.Cu (power_stage(), around tools/place_pack.py's placement): SYS and PMID from U7's
  pins out under their rows of caps, SW1 and SW2 from the pins to L2's pads (SW1 on over C18's SW1 pad), PGND from
  its pin out between L2's pads to a row of vias under L2's body, and short pours from the VBUS, BAT and REGN pins to
  their caps. BTST2 runs straight up to C19 over pin 19, and SW2 from C19 by a via and In2 back to a via beside L2's
  SW2 pad; BTST1 runs from pin 4 to C18 (under L2) by B.Cu; SDRV, SDA, SCL
  and the east ground pins have necks to vias under U7, and VBUS a strip under U7 from its east pins to pins 2 and 3;
  BATP, ILIM_HIZ and TS (U7's crowded north-east corner) and J1's CC2 and north VBUS pads short escapes to vias, and
  C36 (packed) a stub out of its SDRV pad.
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OX, OY = 100.0, 100.0
W, H = 50.0, 23.0
VIA_D, VIA_DRILL = 0.6, 0.3
SMALL_VIA = (0.45, 0.3)         # setup vias where a 0.6 mm one doesn't fit (BTST1 beside pin 4), as the router's
                                # signal vias

PLANE = ["/PACK+", "/BAT_N", "/PACK-"]
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    xo = pin["25"][0]                                    # the pins' outer ends
    sw2, sw1 = box(pad(b, "L2", net="/SW2")), box(pad(b, "L2", net="/SW1"))
    lx0, lx1 = sw2[0], sw2[2]
    xs1 = xo - 0.2                                       # SYS and PMID strips, 0.8 mm wide, beside the pins
    xs0 = xs1 - 0.8
    rx1 = xs0 - 0.2                                      # the SW pours' east edge
    pin_in = xo + 0.5                                    # pours reach this far onto the pins
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    st, sb, sx = min(p[1] for p in sys_pads), max(p[3] for p in sys_pads), min(p[0] for p in sys_pads)
    pt, pb, px = min(p[1] for p in pmid_pads), max(p[3] for p in pmid_pads), min(p[0] for p in pmid_pads)
    assert sb <= sw2[1] - 0.2 and pt >= sw1[3] + 0.2, "a cap row is too close to L2"
    k.pour("F SYS", "/CHG_SYS", [(xs1, y["25"] - 0.1, pin_in, y["25"] + 0.1), (xs0, st, xs1, y["25"] + 0.1),
                                 (sx, st, xs1, sb)])
    k.pour("F PMID", "/PMID", [(xs1, y["29"] - 0.1, pin_in, y["29"] + 0.1), (xs0, y["29"] - 0.1, xs1, pb),
                               (px, pt, xs1, pb)])
    k.pour("F SW2", "/SW2", [(rx1 - 0.4, y["26"] - NECK, pin_in, y["26"] + NECK),
                             (lx1 - 0.3, sw2[1], rx1, y["26"] - NECK)])
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    vias += [sv + ("/SW2",)]
    for x, yy, *net in vias:
        k.via(net[0] if net else "/PACK-", x, yy)
    # SDRV (the NW corner pin) is boxed in by the SYS strip, BAT's pins and C33: a neck east under the BAT pins to a via
    # under U7's body (no exposed pad), clear of pin 25. C36 hangs off the via on another layer.
    sd = box(pad(b, "U7", "24"))
    ny = sd[3] - 0.05                                    # the neck's centre, just inside the pad's inner edge
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    k.path("/PACK-", pcbnew.F_Cu, [(p11[0] + 0.1, y11), (p11[0] - 0.25, y11), ge], 0.2)
    k.path("/PACK-", pcbnew.F_Cu, [(p13[0] + 0.1, y13), (p13[0] - 0.25, y13), ge], 0.2)
    k.via("/PACK-", *ge)
    # the north row's east end, by C19: BATP (pin 18) to a via just north of it, clear of BTST2's straight run up to
    # C19; ILIM_HIZ (pin 17) up and east over TS's corner pad to a via; TS (16) east to a via under J1's courtyard
    p18, p17, p16 = box(pad(b, "U7", "18")), box(pad(b, "U7", "17")), box(pad(b, "U7", "16"))
    x18, x17, top = (p18[0] + p18[2]) / 2, (p17[0] + p17[2]) / 2, p17[1]
    vbp = (x18 + 0.15, top - 0.75)
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    k.track("/VBUS", pcbnew.F_Cu, a9[0] + 0.1, vvb[1], *vvb, 0.3)
    k.via("/CC2", *vcc)
    k.via("/VBUS", *vvb)
    # C19's boot loop, all laid here (the router ran short of lanes for it in every order): BTST2 straight up from pin
    # 19 to C19's BTST2 pad over it, and SW2 from a via just east of C19's SW2 pad on In2 west and down to SW2's via
    p19, b19, c19 = box(pad(b, "U7", "19")), box(pad(b, "C19", net="/BTST2")), box(pad(b, "C19", net="/SW2"))
    k.track("/BTST2", pcbnew.F_Cu, (p19[0] + p19[2]) / 2, p19[1] + 0.1, (p19[0] + p19[2]) / 2, b19[3] - 0.1, 0.15)
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    k.via("/SW2", *vs)
    # ILIM_HIZ (a high-impedance node that sets the input current clamp) stays 1 mm off that run on B.Cu
    k.router_keepout(["/ILIM_HIZ"], (pcbnew.B_Cu,), [seg_poly(a, c, 1.0) for a, c in zip(sw2_run, sw2_run[1:])])
    # BTST1 (pin 4, south side) to C18 under L2: down to a small via beside the pin (C22 sits west of the pins for
    # it), B.Cu west under the PMID strip, up by a via beside C18's BTST1 pad
    p4, bt = box(pad(b, "U7", "4")), box(pad(b, "C18", net="/BTST1"))
    vp = ((p4[0] + p4[2]) / 2 - 0.13, p4[3] + PAD_VIA + SMALL_VIA[0] / 2 + 0.05)
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    k.track("/BTST1", pcbnew.F_Cu, *vc, bt[0] + 0.1, vc[1], 0.15)
    k.via("/BTST1", *vp, SMALL_VIA)
    k.via("/BTST1", *vc, SMALL_VIA)
    # pins to their caps: VBUS (C22), BAT (C33), REGN (C35): over the pins, and down to the cap's pad only as wide as
    # both
    for name, net, pins, cap in (("F VBUS", "/VBUS", ("2", "3"), "C22"), ("F BAT", "/PACK+", ("22", "23"), "C33"),
                                 ("F REGN", "/REGN", ("5",), "C35")):
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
